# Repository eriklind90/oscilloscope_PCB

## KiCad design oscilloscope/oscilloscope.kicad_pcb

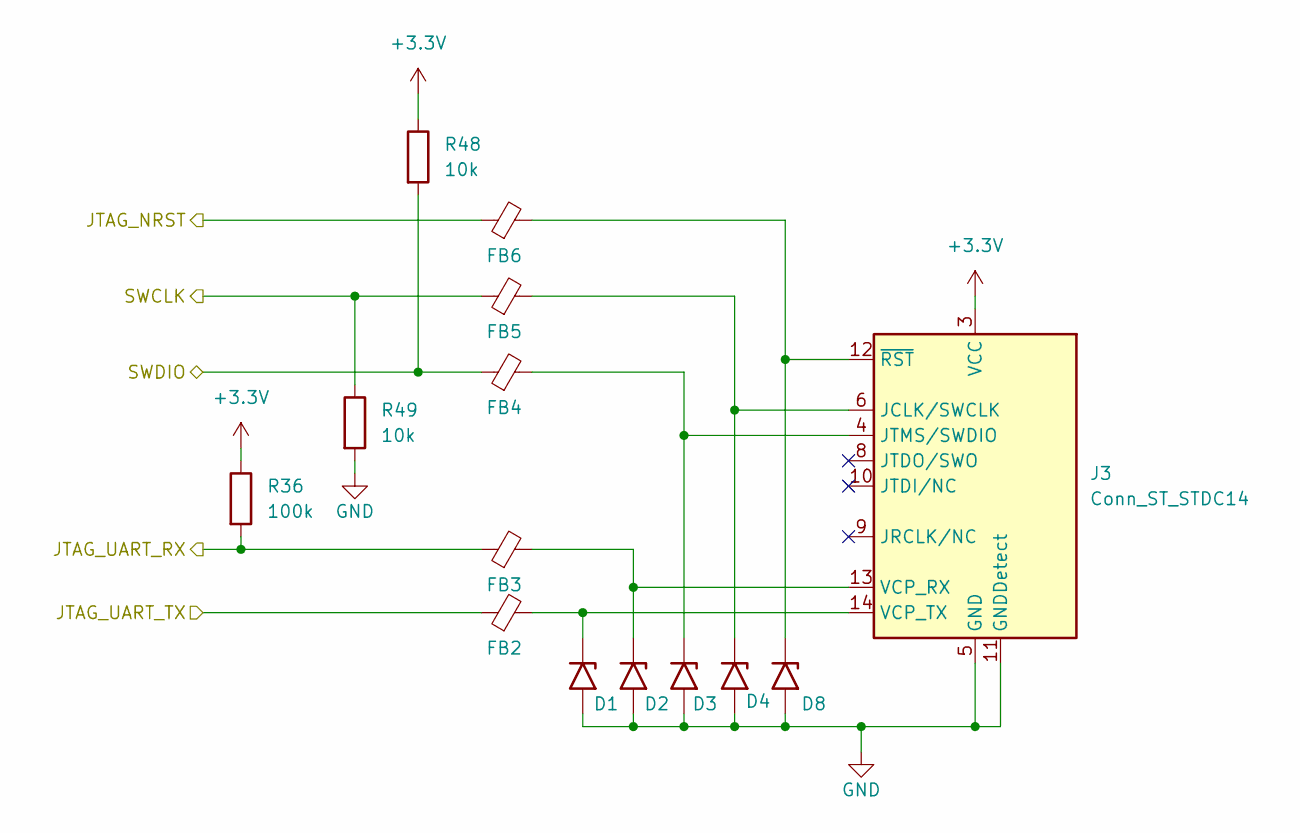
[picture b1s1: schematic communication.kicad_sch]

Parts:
D1, D2, D3, D4, D8: SMF5V0A; D_SMF; LCSC C1972946
FB2, FB3, FB4, FB5, FB6: GZ1608D601TF; R_0603_1608Metric; LCSC C1002
J3: Conn_ST_STDC14; SAMTEC_FTSH-107-01-X-DV-K; LCSC x
R36: 100k; R_0402_1005Metric; LCSC C25741
R48, R49: 10k; R_0402_1005Metric; LCSC C25744

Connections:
+3.3V: J3.3 (VCC), R36.1, R48.1; also elsewhere on the board
/communication/JTAG_NRST: FB6.1; also elsewhere on the board
/communication/JTAG_UART_RX: FB3.1, R36.2; also elsewhere on the board
/communication/JTAG_UART_TX: FB2.1; also elsewhere on the board
/communication/SWDIO: FB4.1, R48.2; also elsewhere on the board
/mcu_main/SWD_CLK: FB5.1, R49.1; also elsewhere on the board
GND: D1.2 (A2), D2.2 (A2), D3.2 (A2), D4.2 (A2), D8.2 (A2), J3.5 (GND), J3.7 (GND), J3.11 (GNDDetect), R49.2; also elsewhere on the board
unnamed: D1.1 (A1), FB2.2, J3.14 (VCP_TX)
unnamed: D2.1 (A1), FB3.2, J3.13 (VCP_RX)
unnamed: D3.1 (A1), FB4.2, J3.4 (JTMS/SWDIO)
unnamed: D4.1 (A1), FB5.2, J3.6 (JCLK/SWCLK)
unnamed: D8.1 (A1), FB6.2, J3.12 (~RST)

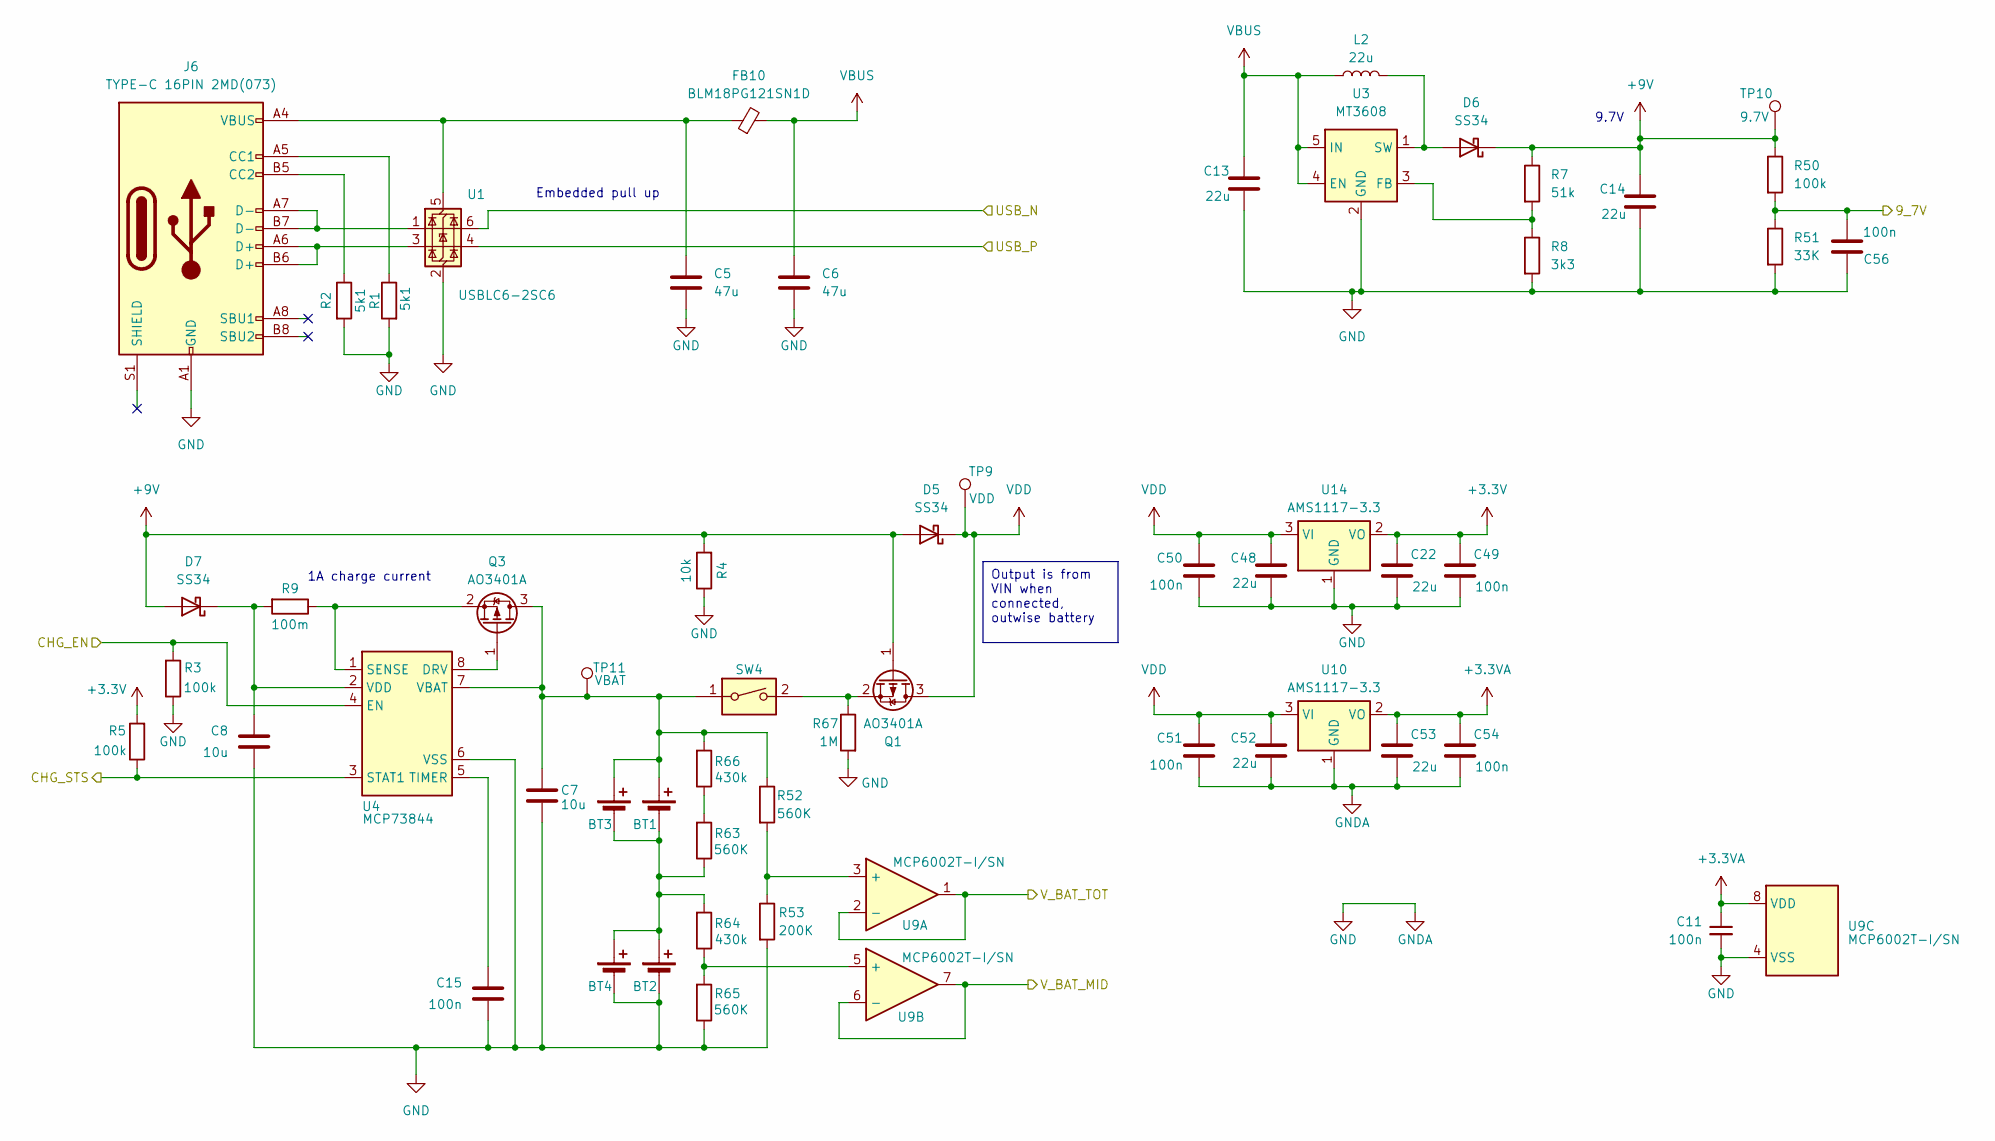
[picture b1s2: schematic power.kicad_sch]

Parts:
BT1, BT2, BT3, BT4: Battery_Cell; BH_18650_1042; LCSC C5249310
C5, C6: 47u; C_1206_3216Metric; LCSC C96123
C7, C8: 10u; C_0603_1608Metric; LCSC C96446
C11, C15, C49, C50, C51, C54, C56: 100n; C_0402_1005Metric; LCSC C307331
C13, C14, C22, C48, C52, C53: 22u; C_0805_2012Metric; LCSC C45783
D5, D6, D7: SS34; D_SMA; LCSC C8678
FB10: BLM18PG121SN1D; R_0603_1608Metric; LCSC C14709
J6: TYPE-C 16PIN 2MD(073); USB_C_Receptacle_HCTL_HC-TYPE-C-16P-01A; LCSC C2894897
L2: 22u; SRN3012BTA; LCSC C19947585
Q1, Q3: AO3401A; SOT-23; LCSC C15127
R1, R2: 5k1; R_0402_1005Metric; LCSC C25905
R3, R5, R50: 100k; R_0402_1005Metric; LCSC C25741
R4: 10k; R_0402_1005Metric; LCSC C25744
R7: 51k; R_0402_1005Metric; LCSC C25794
R8: 3k3; R_0402_1005Metric; LCSC C25890
R9: 100m; R_0402_1005Metric; LCSC x
R51: 33K; R_0402_1005Metric; LCSC C25779
R52, R63, R65: 560K; R_0603_1608Metric; LCSC C23203
R53: 200K; R_0603_1608Metric; LCSC C25811
R64, R66: 430k; R_0603_1608Metric; LCSC C25969
R67: 1M; R_0402_1005Metric; LCSC C26083
SW4: 5055670271; CONN_505567_02_MOL; LCSC x
TP9: VDD; TestPoint_THTPad_1.0x1.0mm_Drill0.5mm; LCSC x
TP10: 9.7V; TestPoint_THTPad_1.0x1.0mm_Drill0.5mm; LCSC x
TP11: VBAT; TestPoint_THTPad_1.0x1.0mm_Drill0.5mm; LCSC x
U1: USBLC6-2SC6; SOT-23-6; LCSC C2827654
U3: MT3608; SOT-23-6; LCSC C84817
U4: MCP73844; MSOP-8_3x3mm_P0.65mm; LCSC x
U9: MCP6002T-I/SN; SOIC-8_3.9x4.9mm_P1.27mm; LCSC C7377
U10, U14: AMS1117-3.3; SOT-223-3_TabPin2; LCSC C6186

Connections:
+3.3V: C22.1, C49.1, R5.2, U14.2 (VO); also elsewhere on the board
+3.3VA: C11.1, C53.1, C54.1, U9.8 (VDD), U10.2 (VO); also elsewhere on the board
+9V: C14.1, D5.2 (A), D6.1 (K), D7.2 (A), Q1.1 (G), R4.2, R7.1, R50.1, TP10.1
/mcu_main/9_7V: C56.2, R50.2, R51.1; also elsewhere on the board
/mcu_main/CHG_EN: R3.2, U4.4 (EN); also elsewhere on the board
/mcu_main/CHG_STS: R5.1, U4.3 (STAT1); also elsewhere on the board
/mcu_main/USB_N: U1.6 (I/O1); also elsewhere on the board
/mcu_main/USB_P: U1.4 (I/O2); also elsewhere on the board
/mcu_main/V_BAT_MID: U9.6 (-), U9.7; also elsewhere on the board
/mcu_main/V_BAT_TOT: U9.1, U9.2 (-); also elsewhere on the board
GND: BT2.2 (-), BT4.2 (-), C5.2, C6.2, C7.2, C8.2, C11.2, C13.2, C14.2, C15.2, C22.2, C48.2, C49.2, C50.2, C51.2, C52.2, C53.2, C54.2, C56.1, J6.A1 (GND), J6.A12 (GND), J6.B1 (GND), J6.B12 (GND), R1.2, R2.2, R3.1, R4.1, R8.2, R51.2, R53.2, R65.1, R67.2, U1.2 (GND), U3.2 (GND), U4.6 (VSS), U9.4 (VSS), U10.1 (GND), U14.1 (GND); also elsewhere on the board
unnamed: BT1.1 (+), BT3.1 (+), C7.1, Q3.3 (D), R52.1, R66.2, SW4.1, TP11.1, U4.7 (VBAT)
unnamed: BT1.2 (-), BT2.1 (+), BT3.2 (-), BT4.1 (+), R63.1, R64.2
unnamed: D6.2 (A), L2.2, U3.1 (SW)
unnamed: C8.1, D7.1 (K), R9.2, U4.2 (VDD)
unnamed: J6.A5 (CC1), R1.1
unnamed: J6.B5 (CC2), R2.1
unnamed: J6.A6 (D+), J6.B6 (D+), U1.3 (I/O2)
unnamed: J6.A7 (D-), J6.B7 (D-), U1.1 (I/O1)
unnamed: Q1.2 (S), R67.1, SW4.2
unnamed: Q3.1 (G), U4.8 (DRV)
unnamed: Q3.2 (S), R9.1, U4.1 (SENSE)
unnamed: R63.2, R66.1
unnamed: C5.1, FB10.1, J6.A4 (VBUS), J6.A9 (VBUS), J6.B4 (VBUS), J6.B9 (VBUS), U1.5 (VBUS)
unnamed: R7.2, R8.1, U3.3 (FB)
unnamed: C15.1, U4.5 (TIMER)
unnamed: R52.2, R53.1, U9.3 (+)
unnamed: R64.1, R65.2, U9.5 (+)
VBUS: C6.1, C13.1, FB10.2, L2.1, U3.4 (EN), U3.5 (IN)
VDD: C48.1, C50.1, C51.1, C52.1, D5.1 (K), Q1.3 (D), TP9.1, U10.3 (VI), U14.3 (VI); also elsewhere on the board

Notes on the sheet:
Output is from VIN when connected, outwise battery
1A charge current
9.7V
Embedded pull up

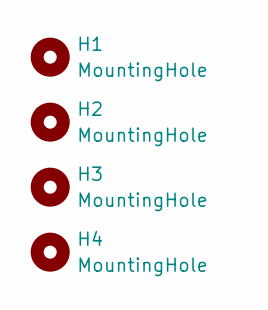
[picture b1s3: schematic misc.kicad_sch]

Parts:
H1, H2, H3, H4: MountingHole; MountingHole_4.3mm_M4_DIN965_Pad_TopBottom; LCSC x

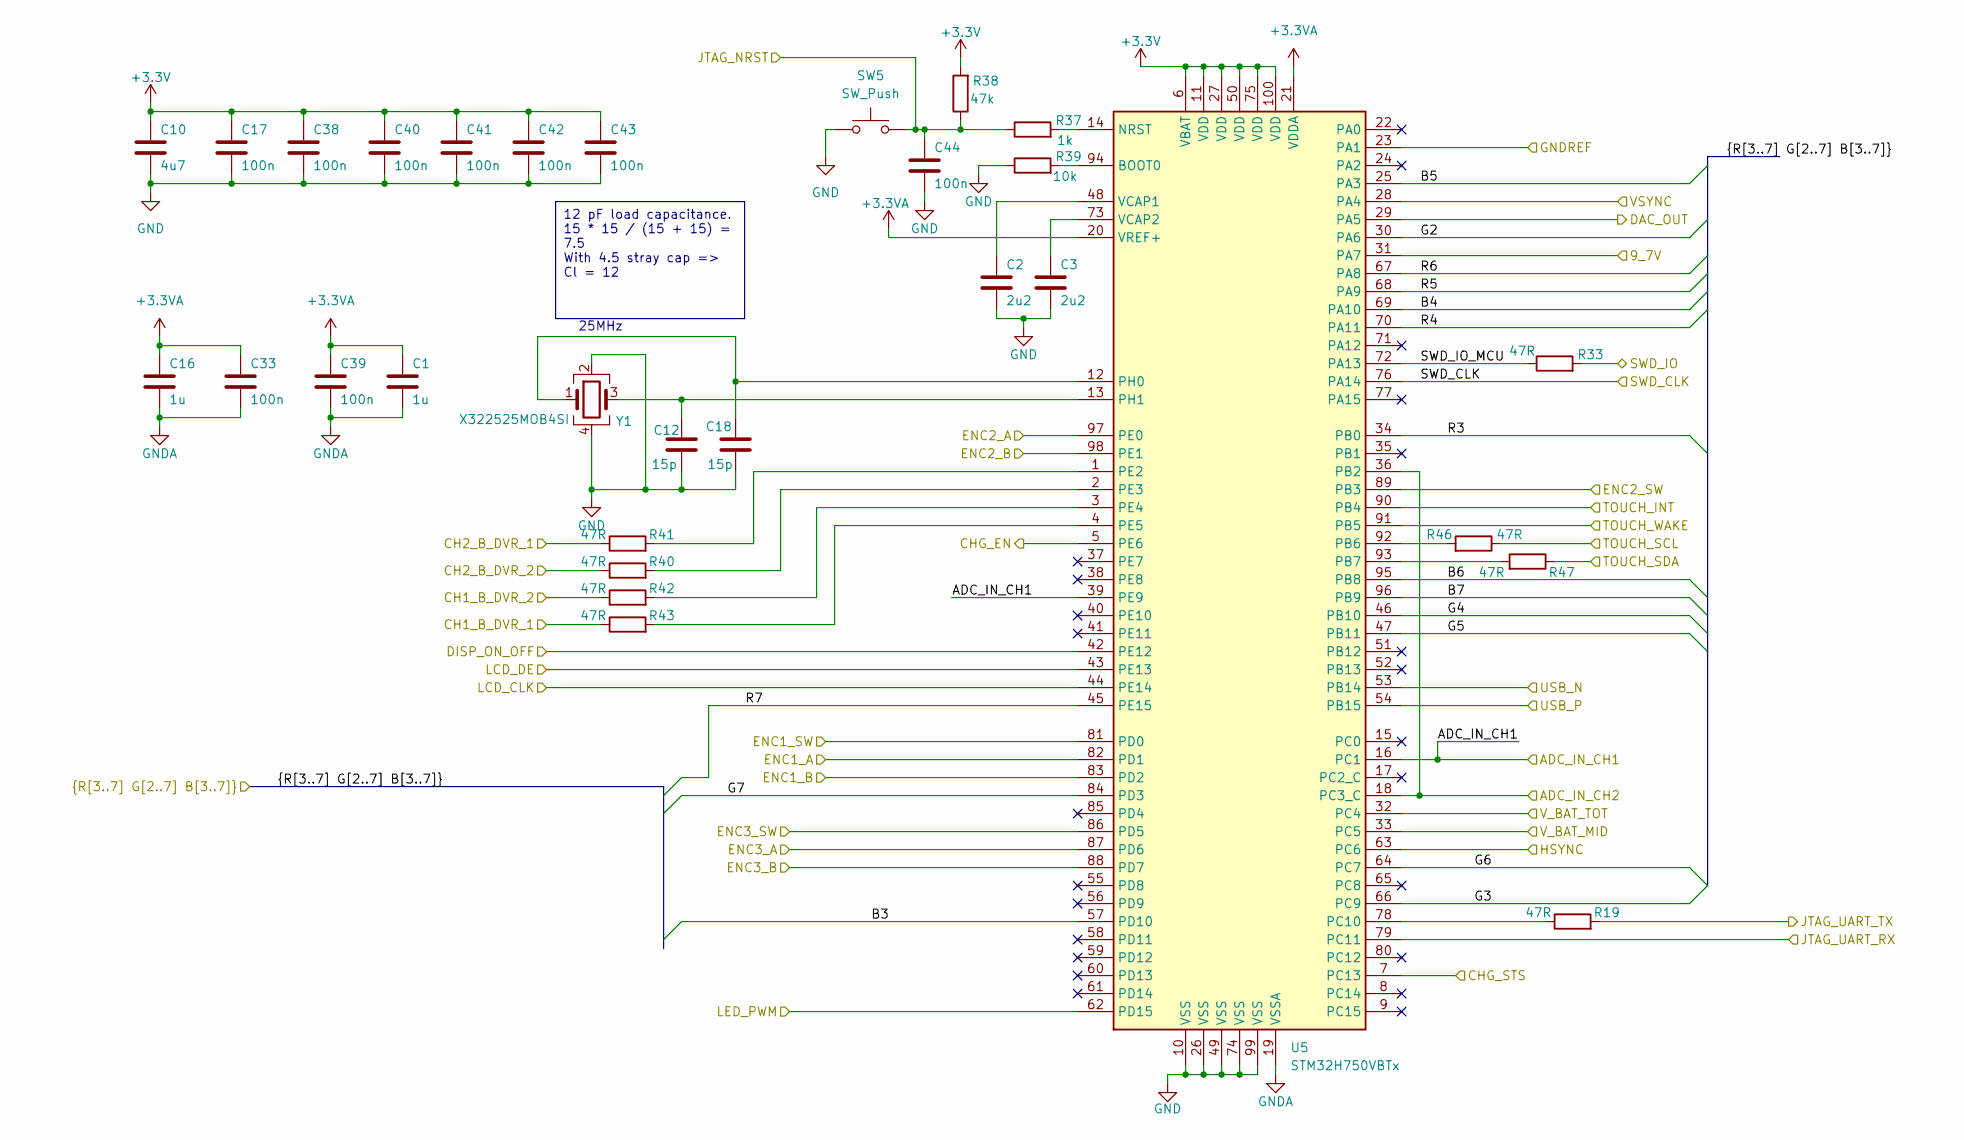
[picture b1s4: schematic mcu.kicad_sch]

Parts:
C1, C16: 1u; C_0402_1005Metric; LCSC C52923
C2, C3: 2u2; C_0402_1005Metric; LCSC C12530
C10: 4u7; C_0603_1608Metric; LCSC C19666
C12, C18: 15p; C_0402_1005Metric; LCSC C1548
C17, C33, C38, C39, C40, C41, C42, C43, C44: 100n; C_0402_1005Metric; LCSC C307331
R19, R33, R40, R41, R42, R43, R46, R47: 47R; R_0402_1005Metric; LCSC C25118
R37: 1k; R_0402_1005Metric; LCSC C11702
R38: 47k; R_0402_1005Metric; LCSC C25792
R39: 10k; R_0402_1005Metric; LCSC C25744
SW5: SW_Push; SW_B3U-1000P; LCSC x
U5: STM32H750VBTx; LQFP-100_14x14mm_P0.5mm; LCSC C404010
Y1: X322525MOB4SI; LCSC C9006

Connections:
+3.3V: C10.1, C17.1, C38.1, C40.1, C41.1, C42.1, C43.1, R38.2, U5.6 (VBAT), U5.11 (VDD), U5.27 (VDD), U5.50 (VDD), U5.75 (VDD), U5.100 (VDD); also elsewhere on the board
+3.3VA: C1.1, C16.1, C33.1, C39.1, U5.20 (VREF+), U5.21 (VDDA); also elsewhere on the board
/Buttons/ENC1_A: U5.82 (PD1); also elsewhere on the board
/Buttons/ENC1_B: U5.83 (PD2); also elsewhere on the board
/Buttons/ENC1_SW: U5.81 (PD0); also elsewhere on the board
/Buttons/ENC2_A: U5.97 (PE0); also elsewhere on the board
/Buttons/ENC2_B: U5.98 (PE1); also elsewhere on the board
/Buttons/ENC2_SW: U5.89 (PB3); also elsewhere on the board
/Buttons/ENC3_A: U5.87 (PD6); also elsewhere on the board
/Buttons/ENC3_B: U5.88 (PD7); also elsewhere on the board
/Buttons/ENC3_SW: U5.86 (PD5); also elsewhere on the board
/Input stage/ADC_IN_CH2: U5.18 (PC3_C), U5.36 (PB2); also elsewhere on the board
/Input stage/CH1_B_DVR_1: R43.1; also elsewhere on the board
/Input stage/CH1_B_DVR_2: R42.1; also elsewhere on the board
/Input stage/CH2_B_DVR_1: R41.1; also elsewhere on the board
/Input stage/CH2_B_DVR_2: R40.1; also elsewhere on the board
/Input stage/DAC_OUT: U5.29 (PA5); also elsewhere on the board
/Screen/B3: U5.57 (PD10); also elsewhere on the board
/Screen/B4: U5.69 (PA10); also elsewhere on the board
/Screen/B5: U5.25 (PA3); also elsewhere on the board
/Screen/B6: U5.95 (PB8); also elsewhere on the board
/Screen/B7: U5.96 (PB9); also elsewhere on the board
/Screen/DISP_ON_OFF: U5.42 (PE12); also elsewhere on the board
/Screen/G2: U5.30 (PA6); also elsewhere on the board
/Screen/G3: U5.66 (PC9); also elsewhere on the board
/Screen/G4: U5.46 (PB10); also elsewhere on the board
/Screen/G5: U5.47 (PB11); also elsewhere on the board
/Screen/G6: U5.64 (PC7); also elsewhere on the board
/Screen/G7: U5.84 (PD3); also elsewhere on the board
/Screen/HSYNC: U5.63 (PC6); also elsewhere on the board
/Screen/LCD_CLK: U5.44 (PE14); also elsewhere on the board
/Screen/LCD_DE: U5.43 (PE13); also elsewhere on the board
/Screen/LED_PWM: U5.62 (PD15); also elsewhere on the board
/Screen/R3: U5.34 (PB0); also elsewhere on the board
/Screen/R4: U5.70 (PA11); also elsewhere on the board
/Screen/R5: U5.68 (PA9); also elsewhere on the board
/Screen/R6: U5.67 (PA8); also elsewhere on the board
/Screen/R7: U5.45 (PE15); also elsewhere on the board
/Screen/TOUCH_INT: U5.90 (PB4); also elsewhere on the board
/Screen/TOUCH_SCL: R46.1; also elsewhere on the board
/Screen/TOUCH_SDA: R47.1; also elsewhere on the board
/Screen/TOUCH_WAKE: U5.91 (PB5); also elsewhere on the board
/Screen/VSYNC: U5.28 (PA4); also elsewhere on the board
/communication/JTAG_NRST: C44.1, R37.1, R38.1, SW5.2; also elsewhere on the board
/communication/JTAG_UART_RX: U5.79 (PC11); also elsewhere on the board
/communication/JTAG_UART_TX: R19.2; also elsewhere on the board
/communication/SWDIO: R33.2; also elsewhere on the board
/mcu_main/9_7V: U5.31 (PA7); also elsewhere on the board
/mcu_main/ADC_IN_CH1: U5.16 (PC1), U5.39 (PE9); also elsewhere on the board
/mcu_main/CHG_EN: U5.5 (PE6); also elsewhere on the board
/mcu_main/CHG_STS: U5.7 (PC13); also elsewhere on the board
/mcu_main/SWD_CLK: U5.76 (PA14); also elsewhere on the board
/mcu_main/SWD_IO_MCU: R33.1, U5.72 (PA13)
/mcu_main/USB_N: U5.53 (PB14); also elsewhere on the board
/mcu_main/USB_P: U5.54 (PB15); also elsewhere on the board
/mcu_main/V_BAT_MID: U5.33 (PC5); also elsewhere on the board
/mcu_main/V_BAT_TOT: U5.32 (PC4); also elsewhere on the board
GND: C1.2, C2.2, C3.2, C10.2, C12.2, C16.2, C17.2, C18.2, C33.2, C38.2, C39.2, C40.2, C41.2, C42.2, C43.2, C44.2, R39.1, SW5.1, U5.10 (VSS), U5.19 (VSSA), U5.26 (VSS), U5.49 (VSS), U5.74 (VSS), U5.99 (VSS), Y1.2, Y1.4; also elsewhere on the board
GNDREF: U5.23 (PA1); also elsewhere on the board
unnamed: R39.2, U5.94 (BOOT0)
unnamed: R37.2, U5.14 (NRST)
unnamed: R46.2, U5.92 (PB6)
unnamed: R47.2, U5.93 (PB7)
unnamed: R19.1, U5.78 (PC10)
unnamed: R41.2, U5.1 (PE2)
unnamed: R40.2, U5.2 (PE3)
unnamed: R42.2, U5.3 (PE4)
unnamed: R43.2, U5.4 (PE5)
unnamed: C18.1, U5.12 (PH0), Y1.1
unnamed: C12.1, U5.13 (PH1), Y1.3
unnamed: C2.1, U5.48 (VCAP1)
unnamed: C3.1, U5.73 (VCAP2)

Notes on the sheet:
12 pF load capacitance. 15 * 15 / (15 + 15) = 7.5 With 4.5 stray cap => Cl = 12
25MHz

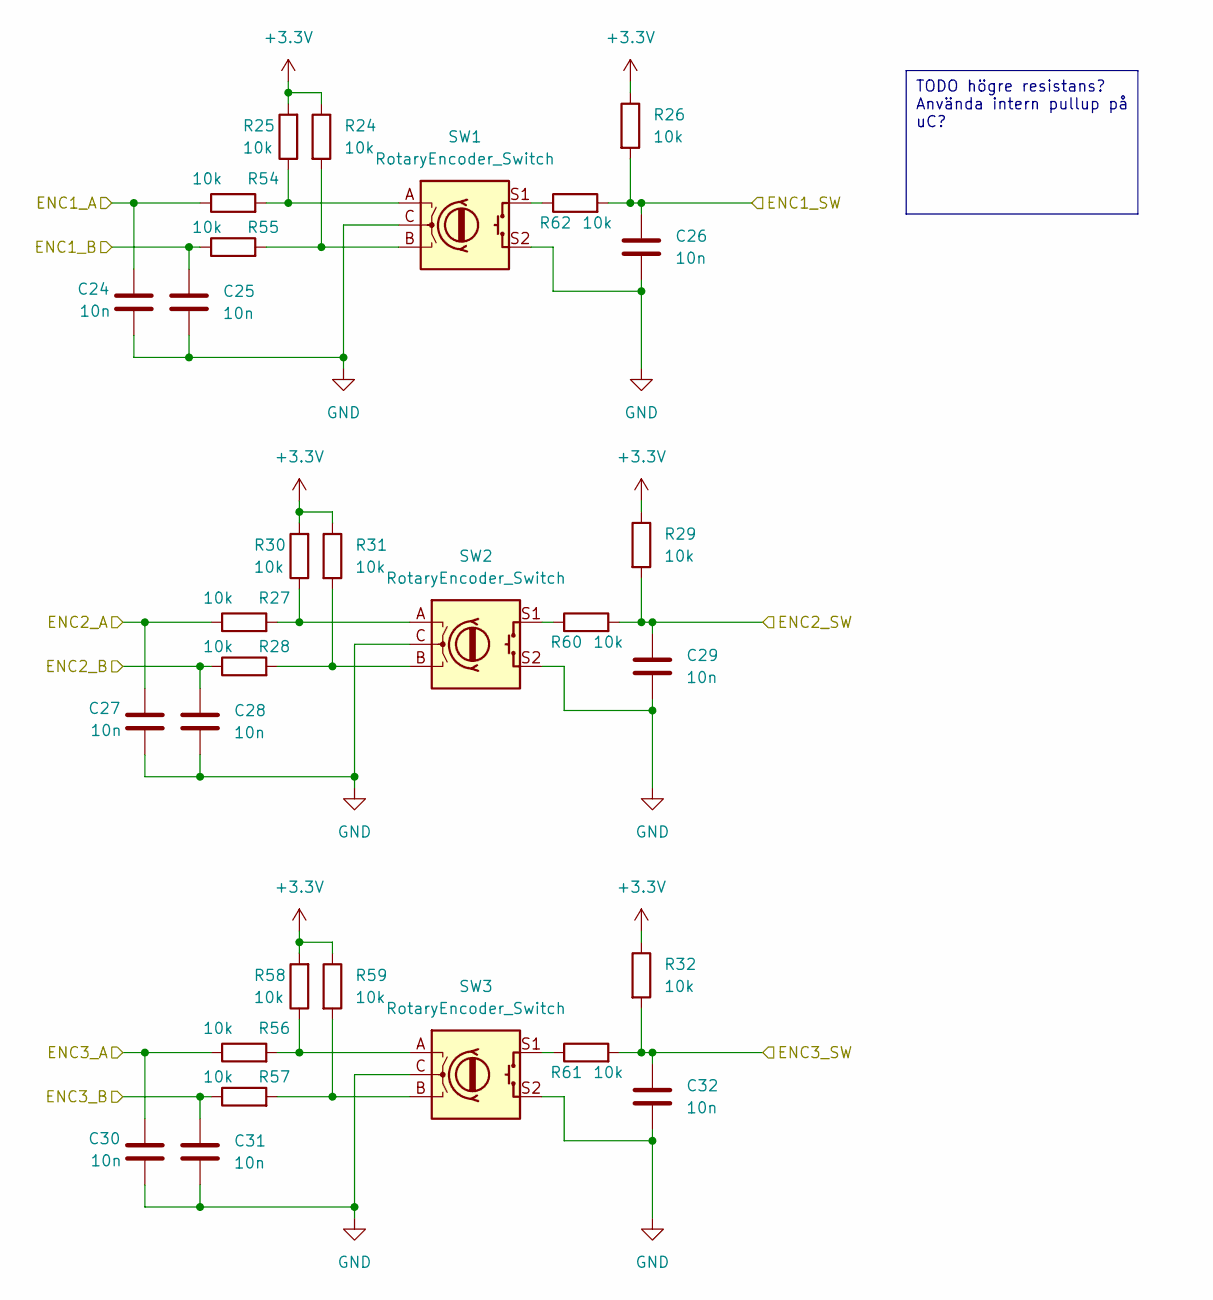
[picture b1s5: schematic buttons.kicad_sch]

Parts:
C24, C25, C26, C27, C28, C29, C30, C31, C32: 10n; C_0402_1005Metric; LCSC C15195
R24, R25, R26, R27, R28, R29, R30, R31, R32, R54, R55, R56, R57, R58, R59, R60, R61, R62: 10k; R_0402_1005Metric; LCSC C25744
SW1, SW2, SW3: RotaryEncoder_Switch; XDCR_PEC12R-2220F-S0024; LCSC x

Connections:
+3.3V: R24.1, R25.2, R26.1, R29.1, R30.2, R31.1, R32.1, R58.2, R59.1; also elsewhere on the board
/Buttons/ENC1_A: C24.1, R54.1; also elsewhere on the board
/Buttons/ENC1_B: C25.1, R55.1; also elsewhere on the board
/Buttons/ENC1_SW: C26.1, R26.2, R62.2; also elsewhere on the board
/Buttons/ENC2_A: C27.1, R27.1; also elsewhere on the board
/Buttons/ENC2_B: C28.1, R28.1; also elsewhere on the board
/Buttons/ENC2_SW: C29.1, R29.2, R60.2; also elsewhere on the board
/Buttons/ENC3_A: C30.1, R56.1; also elsewhere on the board
/Buttons/ENC3_B: C31.1, R57.1; also elsewhere on the board
/Buttons/ENC3_SW: C32.1, R32.2, R61.2; also elsewhere on the board
GND: C24.2, C25.2, C26.2, C27.2, C28.2, C29.2, C30.2, C31.2, C32.2, SW1.C, SW1.S2, SW2.C, SW2.S2, SW3.C, SW3.S2; also elsewhere on the board
unnamed: R24.2, R55.2, SW1.B
unnamed: R25.1, R54.2, SW1.A
unnamed: R27.2, R30.1, SW2.A
unnamed: R28.2, R31.2, SW2.B
unnamed: R56.2, R58.1, SW3.A
unnamed: R57.2, R59.2, SW3.B
unnamed: R60.1, SW2.S1
unnamed: R61.1, SW3.S1
unnamed: R62.1, SW1.S1

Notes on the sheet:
TODO högre resistans? Använda intern pullup på uC?

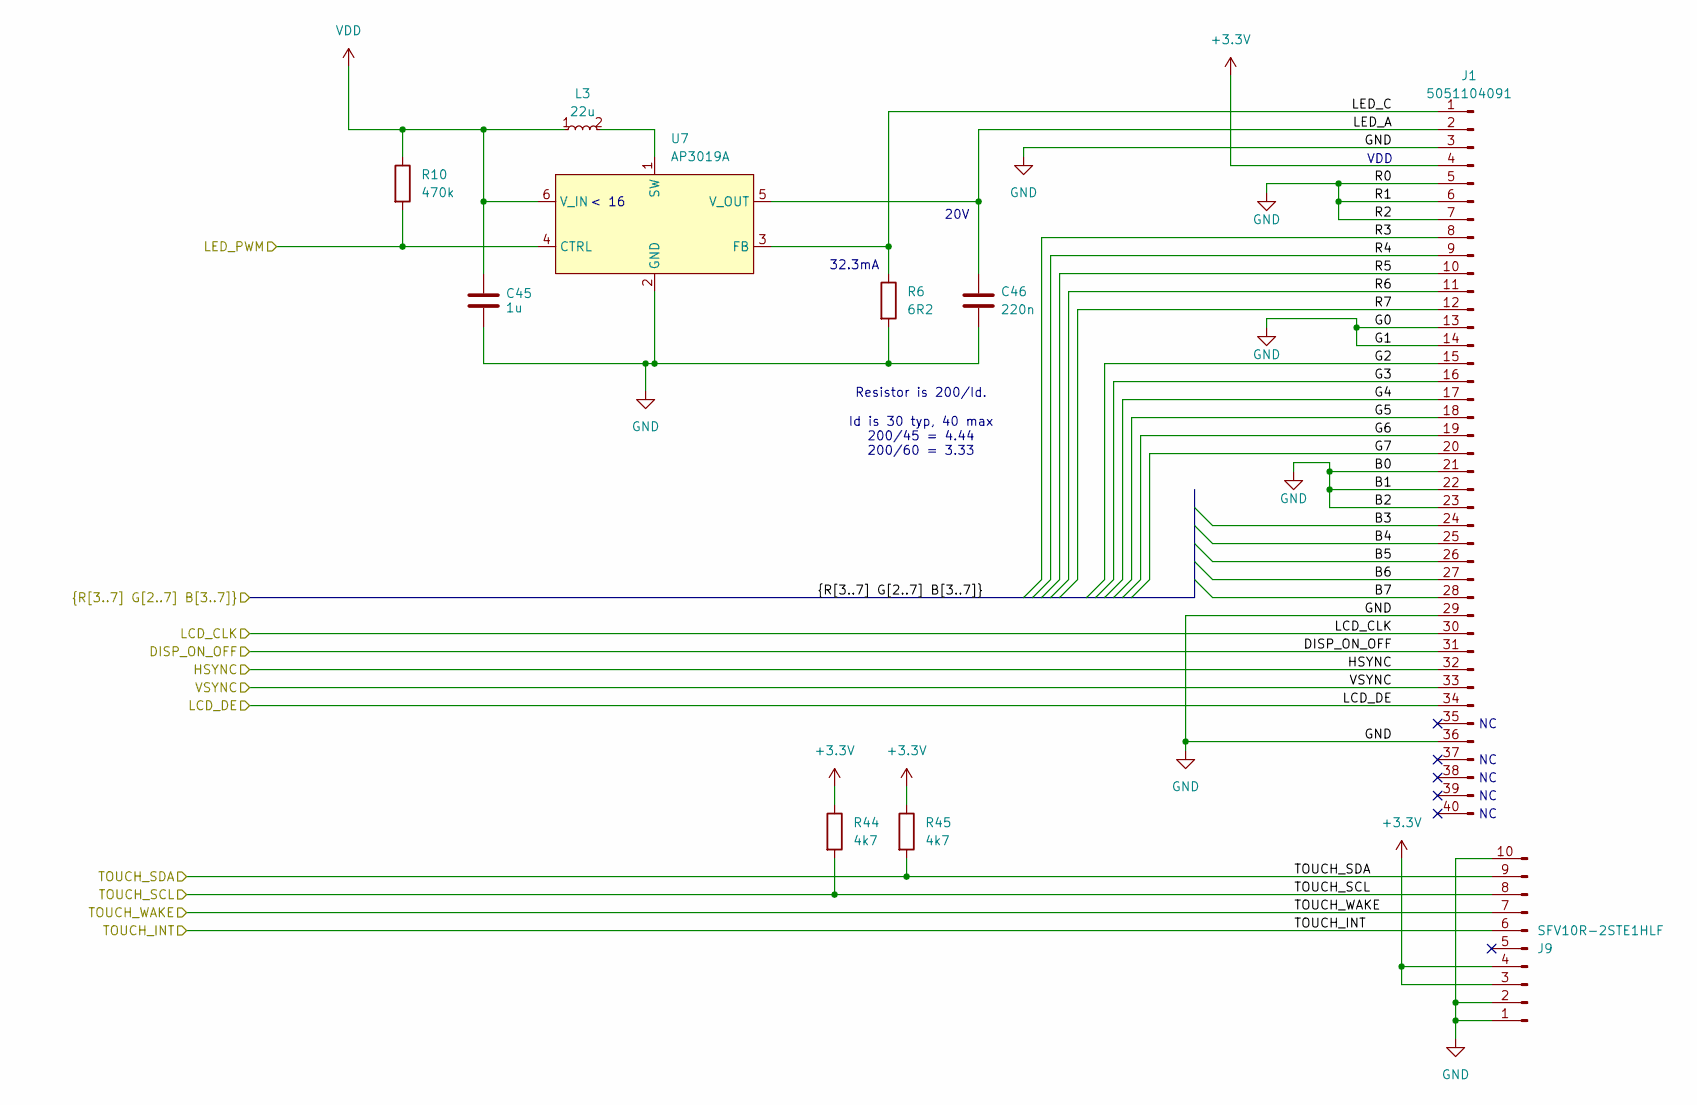
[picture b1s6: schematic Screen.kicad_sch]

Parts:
C45: 1u; C_0402_1005Metric; LCSC C52923
C46: 220n; C_0805_2012Metric; LCSC C5378
J1: 5051104091; CON_5051104091_MOL; LCSC x
J9: SFV10R-2STE1HLF; AMPHENOL_SFV10R-2STE1HLF; LCSC x
L3: 22u; SRN3012BTA; LCSC C19947585
R6: 6R2; R_0805_2012Metric; LCSC x
R10: 470k; R_0402_1005Metric; LCSC C25790
R44, R45: 4k7; R_0402_1005Metric; LCSC C25900
U7: AP3019A; TSOT-23-6; LCSC x

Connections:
+3.3V: J1.4, J9.3, J9.4, R44.1, R45.1; also elsewhere on the board
/Screen/B3: J1.24; also elsewhere on the board
/Screen/B4: J1.25; also elsewhere on the board
/Screen/B5: J1.26; also elsewhere on the board
/Screen/B6: J1.27; also elsewhere on the board
/Screen/B7: J1.28; also elsewhere on the board
/Screen/DISP_ON_OFF: J1.31; also elsewhere on the board
/Screen/G2: J1.15; also elsewhere on the board
/Screen/G3: J1.16; also elsewhere on the board
/Screen/G4: J1.17; also elsewhere on the board
/Screen/G5: J1.18; also elsewhere on the board
/Screen/G6: J1.19; also elsewhere on the board
/Screen/G7: J1.20; also elsewhere on the board
/Screen/HSYNC: J1.32; also elsewhere on the board
/Screen/LCD_CLK: J1.30; also elsewhere on the board
/Screen/LCD_DE: J1.34; also elsewhere on the board
/Screen/LED_A: C46.1, J1.2, U7.5 (V_OUT)
/Screen/LED_C: J1.1, R6.1, U7.3 (FB)
/Screen/LED_PWM: R10.2, U7.4 (CTRL); also elsewhere on the board
/Screen/R3: J1.8; also elsewhere on the board
/Screen/R4: J1.9; also elsewhere on the board
/Screen/R5: J1.10; also elsewhere on the board
/Screen/R6: J1.11; also elsewhere on the board
/Screen/R7: J1.12; also elsewhere on the board
/Screen/TOUCH_INT: J9.6; also elsewhere on the board
/Screen/TOUCH_SCL: J9.8, R44.2; also elsewhere on the board
/Screen/TOUCH_SDA: J9.9, R45.2; also elsewhere on the board
/Screen/TOUCH_WAKE: J9.7; also elsewhere on the board
/Screen/VSYNC: J1.33; also elsewhere on the board
GND: C45.2, C46.2, J1.3, J1.5, J1.6, J1.7, J1.13, J1.14, J1.21, J1.22, J1.23, J1.29, J1.36, J9.1, J9.2, J9.10, R6.2, U7.2 (GND); also elsewhere on the board
unnamed: L3.2, U7.1 (SW)
VDD: C45.1, L3.1, R10.1, U7.6 (V_IN); also elsewhere on the board

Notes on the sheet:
Resistor is 200/Id. Id is 30 typ, 40 max 200/45 = 4.44 200/60 = 3.33
VDD
32.3mA
< 16
20V

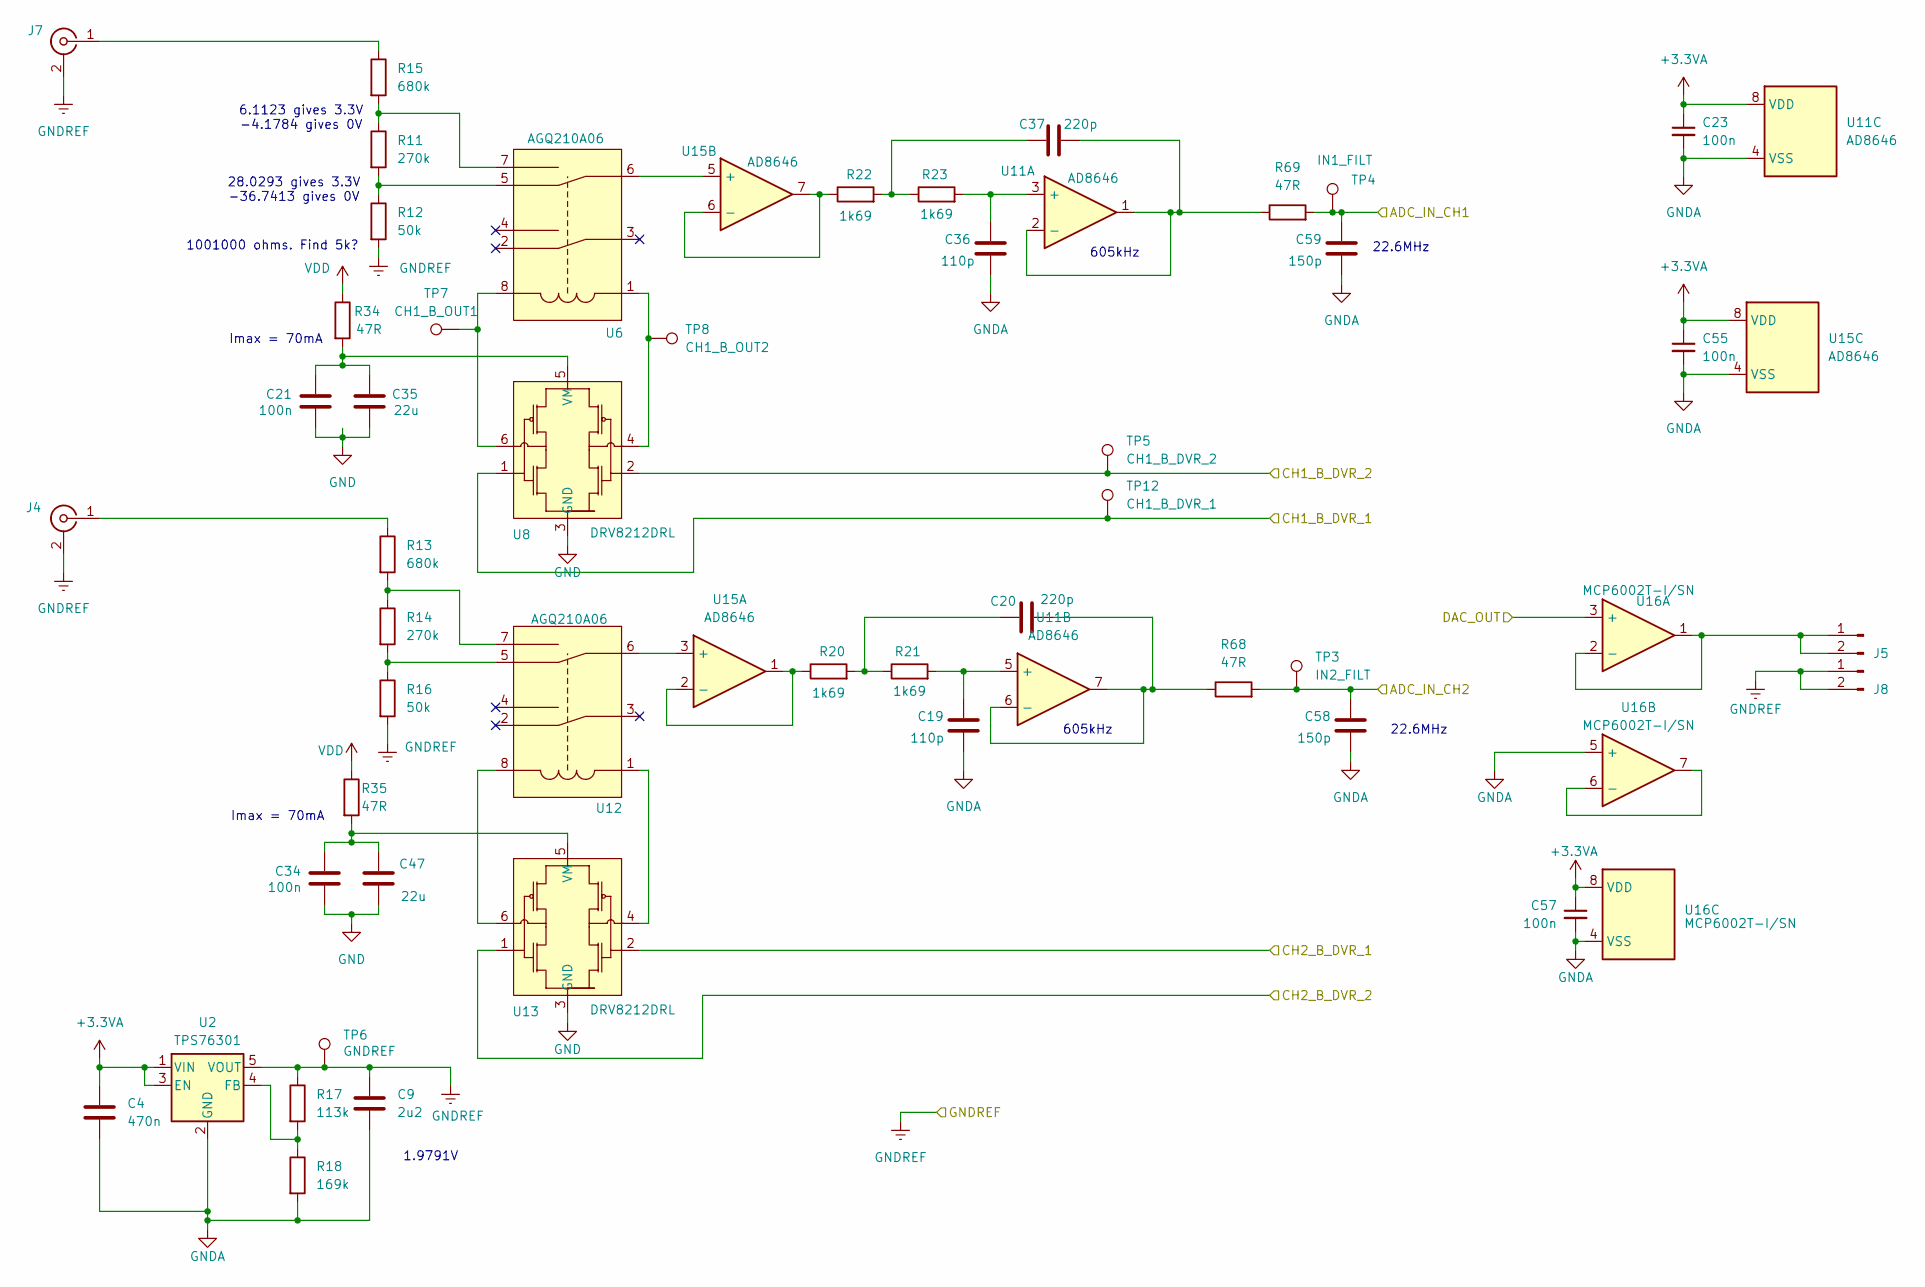
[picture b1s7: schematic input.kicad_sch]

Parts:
C4: 470n; C_0603_1608Metric; LCSC C1623
C9: 2u2; C_0603_1608Metric; LCSC C23630
C19, C36: 110p; C_0603_1608Metric; LCSC C519568
C20, C37: 220p; C_0603_1608Metric; LCSC C519500
C21, C34: 100n; C_0603_1608Metric; LCSC C14663
C23, C55, C57: 100n; C_0402_1005Metric; LCSC C307331
C35, C47: 22u; C_0805_2012Metric; LCSC C45783
C58, C59: 150p; C_0603_1608Metric; LCSC C1594
J4, J7: Conn_Coaxial; LINX_CONBNC002; LCSC x
J5, J8: Conn_01x02_Pin; PinHeader_1x02_P2.54mm_Vertical; LCSC x
R11, R14: 270k; R_0603_1608Metric; LCSC x
R12, R16: 50k; R_0603_1608Metric; LCSC x
R13, R15: 680k; R_0603_1608Metric; LCSC x
R17: 113k; R_0603_1608Metric; LCSC x
R18: 169k; R_0603_1608Metric; LCSC x
R20, R21, R22, R23: 1k69; R_0603_1608Metric; LCSC x
R34, R35: 47R; R_0805_2012Metric; LCSC C17714
R68, R69: 47R; R_0603_1608Metric; LCSC C23182
TP3: IN2_FILT; TestPoint_THTPad_1.0x1.0mm_Drill0.5mm; LCSC x
TP4: IN1_FILT; TestPoint_THTPad_1.0x1.0mm_Drill0.5mm; LCSC x
TP5: CH1_B_DVR_2; TestPoint_THTPad_1.0x1.0mm_Drill0.5mm; LCSC x
TP6: GNDREF; TestPoint_THTPad_1.0x1.0mm_Drill0.5mm; LCSC x
TP7: CH1_B_OUT1; TestPoint_THTPad_1.0x1.0mm_Drill0.5mm; LCSC x
TP8: CH1_B_OUT2; TestPoint_THTPad_1.0x1.0mm_Drill0.5mm; LCSC x
TP12: CH1_B_DVR_1; TestPoint_THTPad_1.0x1.0mm_Drill0.5mm; LCSC x
U2: TPS76301; SOT-23-5; LCSC x
U6, U12: AGQ210A06; AGQ21TA03X; LCSC x
U8, U13: DRV8212DRL; SOT6_DRV8212_TEX; LCSC x
U11, U15: AD8646; SOIC-8_3.9x4.9mm_P1.27mm; LCSC x
U16: MCP6002T-I/SN; SOIC-8_3.9x4.9mm_P1.27mm; LCSC C7377

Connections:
+3.3VA: C4.1, C23.1, C55.1, C57.1, U2.1 (VIN), U2.3 (EN), U11.8 (VDD), U15.8 (VDD), U16.8 (VDD); also elsewhere on the board
/Input stage/ADC_IN_CH2: C58.1, R68.2, TP3.1; also elsewhere on the board
/Input stage/CH1_B_DVR_1: TP12.1, U8.1 (IN1); also elsewhere on the board
/Input stage/CH1_B_DVR_2: TP5.1, U8.2 (IN1); also elsewhere on the board
/Input stage/CH2_B_DVR_1: U13.2 (IN1); also elsewhere on the board
/Input stage/CH2_B_DVR_2: U13.1 (IN1); also elsewhere on the board
/Input stage/DAC_OUT: U16.3 (+); also elsewhere on the board
/mcu_main/ADC_IN_CH1: C59.1, R69.2, TP4.1; also elsewhere on the board
GND: C4.2, C9.2, C19.2, C21.1, C23.2, C34.1, C35.2, C36.2, C47.2, C55.2, C57.2, C58.2, C59.2, R18.2, U2.2 (GND), U8.3 (GND), U11.4 (VSS), U13.3 (GND), U15.4 (VSS), U16.4 (VSS), U16.5 (+); also elsewhere on the board
GNDREF: C9.1, J4.2 (Ext), J7.2 (Ext), J8.1, J8.2, R12.2, R16.2, R17.1, TP6.1, U2.5 (VOUT); also elsewhere on the board
unnamed: C20.1, R20.2, R21.1
unnamed: C37.1, R22.2, R23.1
unnamed: J4.1 (In), R13.1
unnamed: J5.1, J5.2, U16.1, U16.2 (-)
unnamed: J7.1 (In), R15.1
unnamed: R11.1, R15.2, U6.7 (OUTB1)
unnamed: R11.2, R12.1, U6.5 (OUTB1)
unnamed: R13.2, R14.1, U12.7 (OUTB1)
unnamed: R14.2, R16.1, U12.5 (OUTB1)
unnamed: R17.2, R18.1, U2.4 (FB)
unnamed: TP7.1, U6.8 (+), U8.6 (OUT1)
unnamed: TP8.1, U6.1 (-), U8.4 (OUT2)
unnamed: C21.2, C35.1, R34.2, U8.5 (VM)
unnamed: C36.1, R23.2, U11.3 (+)
unnamed: C37.2, R69.1, U11.1, U11.2 (-)
unnamed: C19.1, R21.2, U11.5 (+)
unnamed: C20.2, R68.1, U11.6 (-), U11.7
unnamed: U12.8 (+), U13.6 (OUT1)
unnamed: U12.1 (-), U13.4 (OUT2)
unnamed: U12.6 (INB), U15.3 (+)
unnamed: C34.2, C47.1, R35.2, U13.5 (VM)
unnamed: R20.1, U15.1, U15.2 (-)
unnamed: U6.6 (INB), U15.5 (+)
unnamed: R22.1, U15.6 (-), U15.7
unnamed: U16.6 (-), U16.7
VDD: R34.1, R35.1; also elsewhere on the board

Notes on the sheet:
1001000 ohms. Find 5k?
28.0293 gives 3.3V -36.7413 gives 0V
6.1123 gives 3.3V -4.1784 gives 0V
605kHz
Imax = 70mA
1.9791V
22.6MHz
605kHz
